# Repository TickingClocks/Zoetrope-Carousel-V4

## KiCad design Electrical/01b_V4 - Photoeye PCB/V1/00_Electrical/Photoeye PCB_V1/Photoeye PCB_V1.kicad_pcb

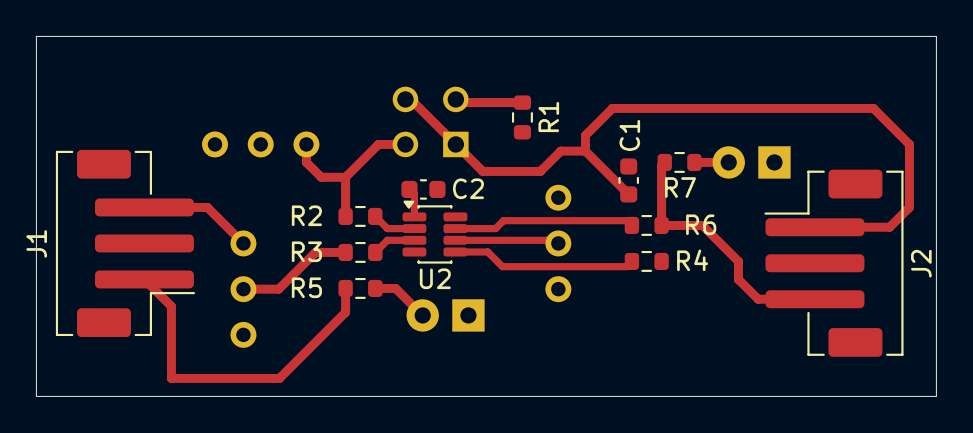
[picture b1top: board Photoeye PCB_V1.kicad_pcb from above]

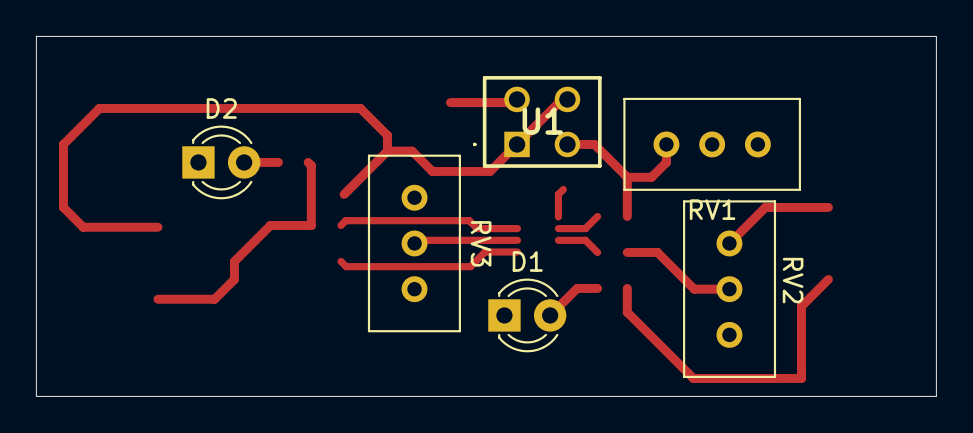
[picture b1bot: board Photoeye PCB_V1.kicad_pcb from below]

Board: 2 copper layers, 50.0 x 20.0 mm, 18 parts (6 on the bottom side), 15 nets.

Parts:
C1: 0.1uF 0603; C_0603_1608Metric
C2: cap; C_0603_1608Metric
D1: YELLOW_3mm_LED; LED_D3.0mm_Clear
D2: GREEN_3mm_TH; LED_D3.0mm
J1, J2: B3B-PH-SM4-TB(LF)(SN); JST_PH_B3B-PH-SM4-TB_1x03-1MP_P2.00mm_Vertical
R1: 100ohm_0603; R_0603_1608Metric
R2, R3, R4, R6: 1kohm_0603; R_0603_1608Metric
R5: ohm_0603; R_0603_1608Metric
R7: 300ohm_0603; R_0603_1608Metric
RV1: 100kohm pot; Potentiometer_Bourns_3296W_Vertical
RV2, RV3: R_Potentiometer_US; Potentiometer_Bourns_3296W_Vertical
U1: RPR-220; RPR220
U2: LM358B; SOT-23-8

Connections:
+3.3V: C1.1, J1.1, J2.1, R5.1, RV3.1, U1.1 (A), U1.3 (E), U2.8 (V+)
/outputState: J2.3, R6.1, R7.2
/platterSensor: R2.2, RV1.1, U1.4 (C)
GND: C1.2, C2.1, D1.1 (K), D2.1 (K), J1.2, J1.MP (Pin_1), J2.2, J2.MP (Pin_1), R1.1, RV1.2, RV2.3, RV3.3, U2.4 (V-)
unnamed: C2.2, R4.2, U2.1
unnamed: D1.2 (A), R5.2
unnamed: D2.2 (A), R7.1
unnamed: J1.3, RV2.1
unnamed: R3.2, RV2.2
unnamed: R6.2, U2.7
unnamed: R1.2, U1.2 (K)
unnamed: R3.1, U2.3 (+)
unnamed: R2.1, U2.2 (-)
unnamed: R4.1, U2.5 (+)
unnamed: RV3.2, U2.6 (-)

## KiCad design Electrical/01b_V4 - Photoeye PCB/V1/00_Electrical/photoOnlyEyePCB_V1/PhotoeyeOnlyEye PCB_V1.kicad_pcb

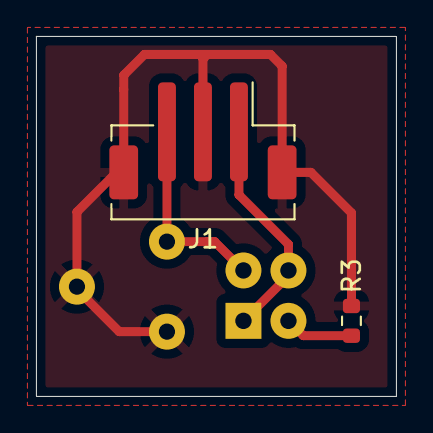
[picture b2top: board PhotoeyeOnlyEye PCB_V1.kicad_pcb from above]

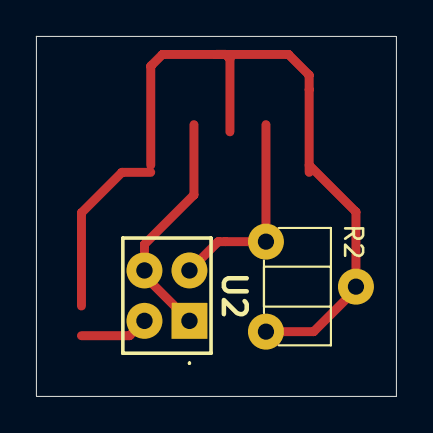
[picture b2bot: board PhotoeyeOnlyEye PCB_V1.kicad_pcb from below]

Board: 2 copper layers, 20.0 x 20.0 mm, 4 parts (2 on the bottom side), 4 nets.

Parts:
J1: B3B-PH-SM4-TB(LF)(SN); JST_PH_B3B-PH-SM4-TB_1x03-1MP_P2.00mm_Vertical
R2: 100k_TH_Pot; Potentiometer_TH
R3: 100ohm_0603; R_0603_1608Metric
U2: RPR-220; RPR220

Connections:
+3.3V: J1.1, U2.1 (A), U2.3 (E)
/sensorValue: J1.3, R2.1, U2.4 (C)
GND: J1.2, J1.MP (Pin_1), R2.2, R2.3, R3.1
unnamed: R3.2, U2.2 (K)

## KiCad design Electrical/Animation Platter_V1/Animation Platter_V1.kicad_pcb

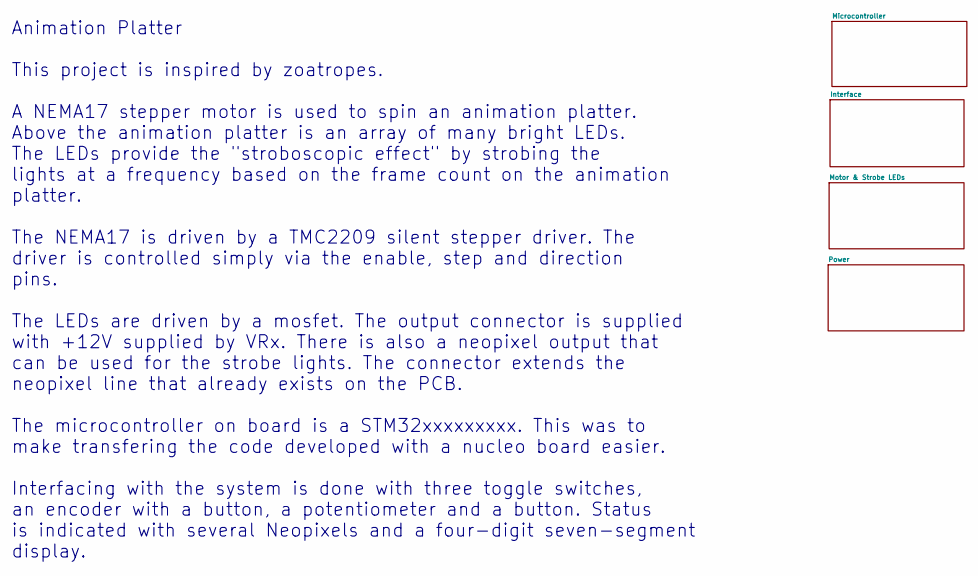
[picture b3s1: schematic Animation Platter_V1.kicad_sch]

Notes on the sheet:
Animation Platter This project is inspired by zoatropes. A NEMA17 stepper motor is used to spin an animation platter. Above the animation platter is an array of many bright LEDs. The LEDs provide the "stroboscopic effect" by strobing the lights at a frequency based on the frame count on the animati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

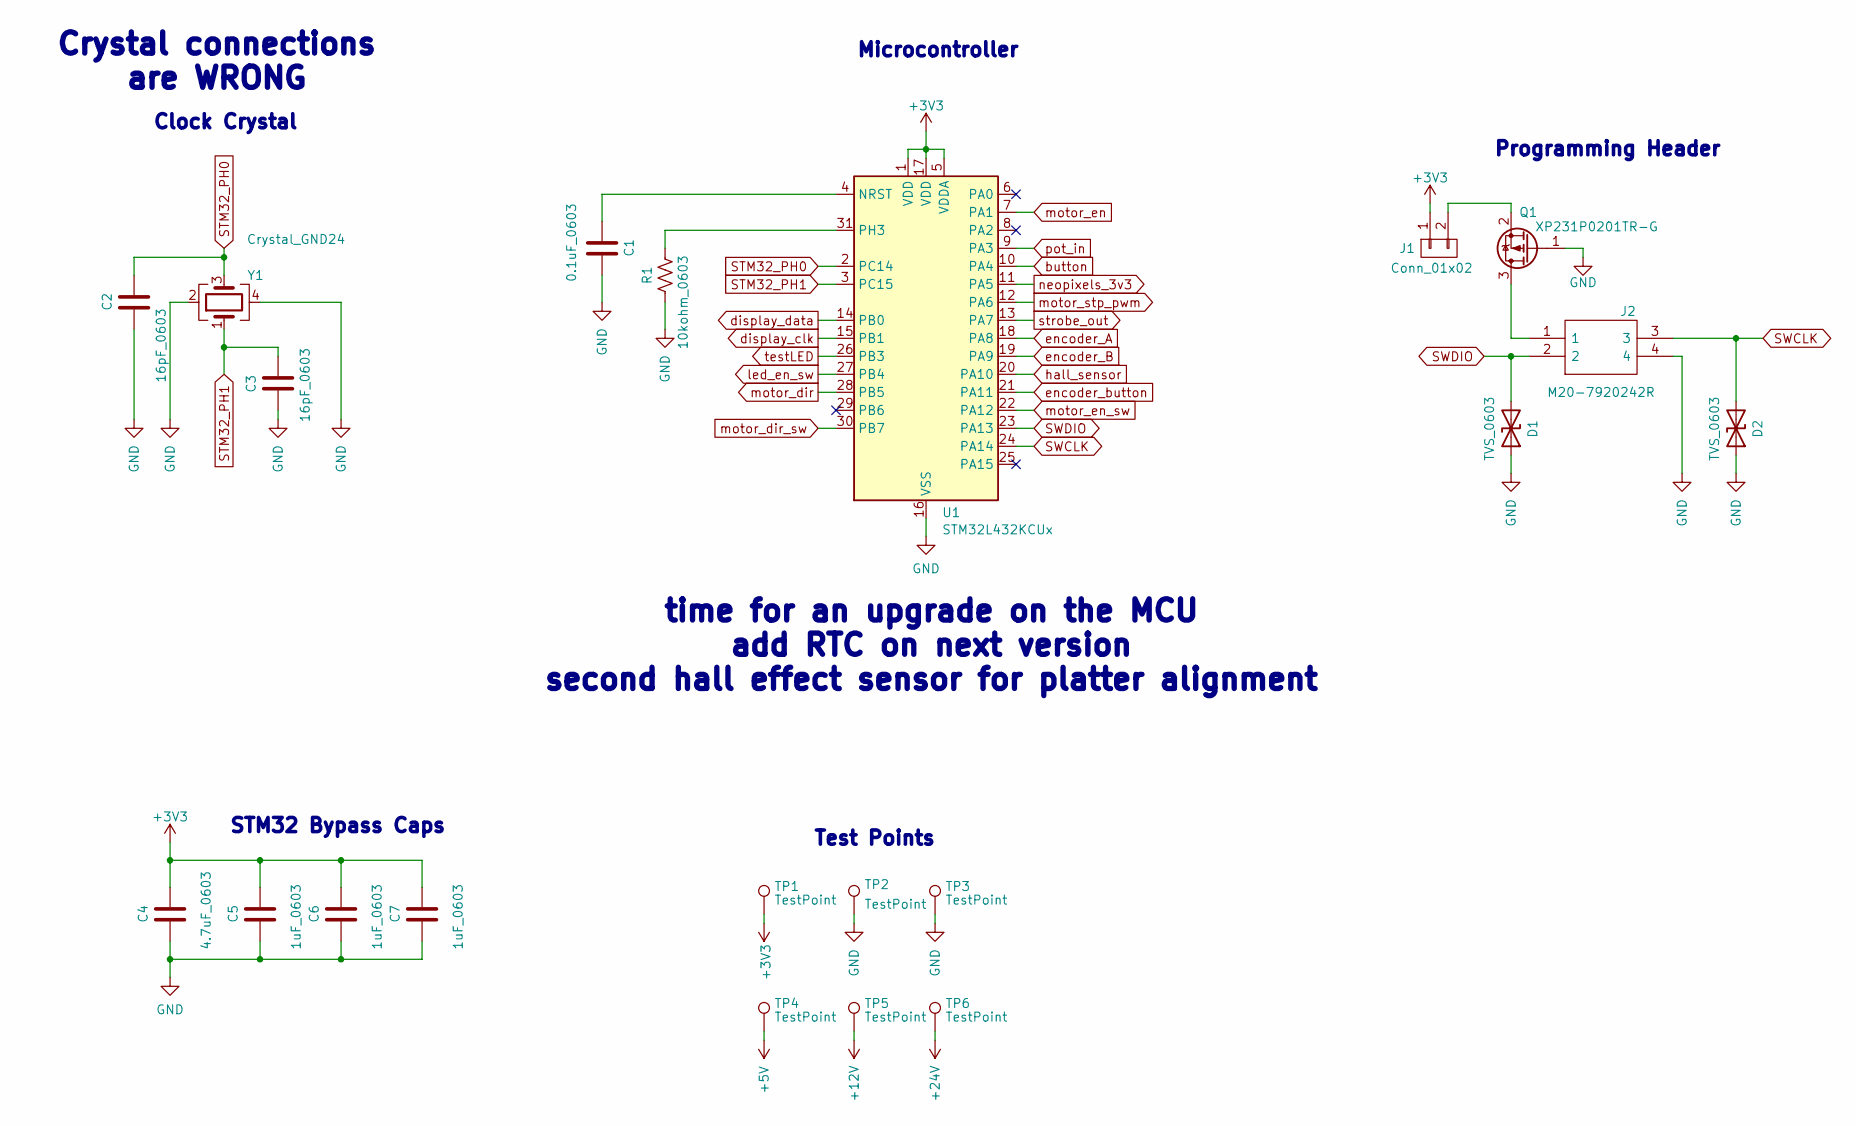
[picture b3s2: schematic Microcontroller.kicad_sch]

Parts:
C1: 0.1uF_0603; C_0603_1608Metric
C2, C3: 16pF_0603; C_0603_1608Metric
C4: 4.7uF_0603; C_0603_1608Metric
C5, C6, C7: 1uF_0603; C_0603_1608Metric
D1, D2: TVS_0603; D_0603_1608Metric
J1: Conn_01x02; PinHeader_1x02_P2.54mm_Vertical
J2: M20-7920242R; M207920242R; Mouser Part Number 855-M20-7920242R
Q1: XP231P0201TR-G; SOT95P240X115-3N
R1: 10kohm_0603; R_0603_1608Metric
TP1, TP4, TP5, TP6: TestPoint; TestPoint_Pad_D1.0mm
TP2, TP3: TestPoint; TestPoint_THTPad_D2.0mm_Drill1.0mm
U1: STM32L432KCUx; QFN-32-1EP_5x5mm_P0.5mm_EP3.45x3.45mm
Y1: Crystal_GND24; Crystal_SMD_2520-4Pin_2.5x2.0mm

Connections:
+3V3: C4.1, C5.1, C6.1, C7.1, J1.1, TP1.1, U1.1 (VDD), U1.5 (VDDA), U1.17 (VDD); also elsewhere on the board
+5V: TP4.1; also elsewhere on the board
+12V: TP5.1; also elsewhere on the board
+24V: TP6.1; also elsewhere on the board
GND: C1.2, C2.2, C3.1, C4.2, C5.2, C6.2, C7.2, D1.1 (A1), D2.1 (A1), J2.4, Q1.1 (G), R1.1, TP2.1, TP3.1, U1.16 (VSS), U1.32 (VSS), U1.33 (VSS), Y1.2, Y1.4; also elsewhere on the board
unnamed: J1.2, Q1.2 (S)
unnamed: J2.1, Q1.3 (D)
unnamed: C1.1, U1.4 (NRST)
unnamed: R1.2, U1.31 (PH3)
STM32_PH0: C2.1, U1.2 (PC14), Y1.3
STM32_PH1: C3.2, U1.3 (PC15), Y1.1
SWCLK: D2.2 (A2), J2.3, U1.24 (PA14)
SWDIO: D1.2 (A2), J2.2, U1.23 (PA13)
button: U1.10 (PA4); also elsewhere on the board
display_clk: U1.15 (PB1); also elsewhere on the board
display_data: U1.14 (PB0); also elsewhere on the board
encoder_A: U1.18 (PA8); also elsewhere on the board
encoder_B: U1.19 (PA9); also elsewhere on the board
encoder_button: U1.21 (PA11); also elsewhere on the board
hall_sensor: U1.20 (PA10); also elsewhere on the board
led_en_sw: U1.27 (PB4); also elsewhere on the board
motor_dir: U1.28 (PB5); also elsewhere on the board
motor_dir_sw: U1.30 (PB7); also elsewhere on the board
motor_en: U1.7 (PA1); also elsewhere on the board
motor_en_sw: U1.22 (PA12); also elsewhere on the board
motor_stp_pwm: U1.12 (PA6); also elsewhere on the board
neopixels_3v3: U1.11 (PA5); also elsewhere on the board
pot_in: U1.9 (PA3); also elsewhere on the board
strobe_out: U1.13 (PA7); also elsewhere on the board
testLED: U1.26 (PB3); also elsewhere on the board

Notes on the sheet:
time for an upgrade on the MCU add RTC on next version second hall effect sensor for platter alignment
STM32 Bypass Caps
Clock Crystal
Crystal connections are WRONG
Microcontroller
Test Points
Programming Header

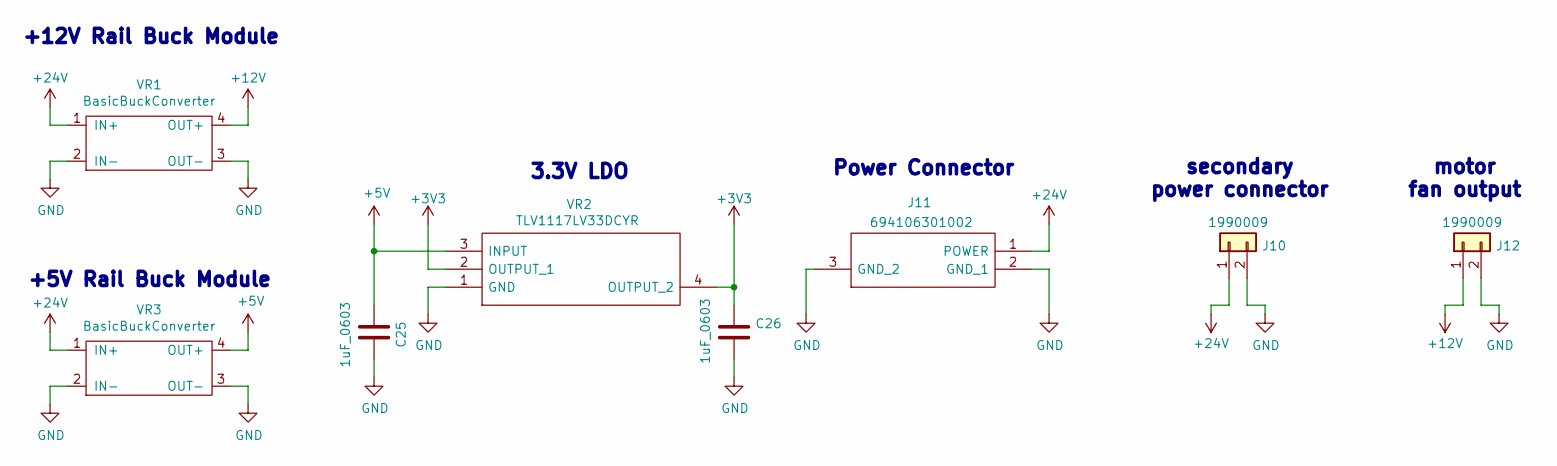
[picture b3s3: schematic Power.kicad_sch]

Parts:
C25, C26: 1uF_0603; C_0603_1608Metric
J10, J12: 1990009
J11: 694106301002; 694106301002_1; Mouser Part Number 710-694106301002
VR1, VR3: BasicBuckConverter; LM2596_Module(43mmx21mm)
VR2: TLV1117LV33DCYR; SOT230P700X180-4N; Mouser Part Number 595-TLV1117LV33DCYR

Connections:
+3V3: C26.2, VR2.2 (OUTPUT_1), VR2.4 (OUTPUT_2); also elsewhere on the board
+5V: C25.2, VR2.3 (INPUT), VR3.4 (OUT+); also elsewhere on the board
+12V: J12.1, VR1.4 (OUT+); also elsewhere on the board
+24V: J10.1, J11.1 (POWER), VR1.1 (IN+), VR3.1 (IN+); also elsewhere on the board
GND: C25.1, C26.1, J10.2, J11.2 (GND_1), J11.3 (GND_2), J12.2, VR1.2 (IN-), VR1.3 (OUT-), VR2.1 (GND), VR3.2 (IN-), VR3.3 (OUT-); also elsewhere on the board

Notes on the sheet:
+12V Rail Buck Module
+5V Rail Buck Module
secondary power connector
3.3V LDO
motor fan output
Power Connector

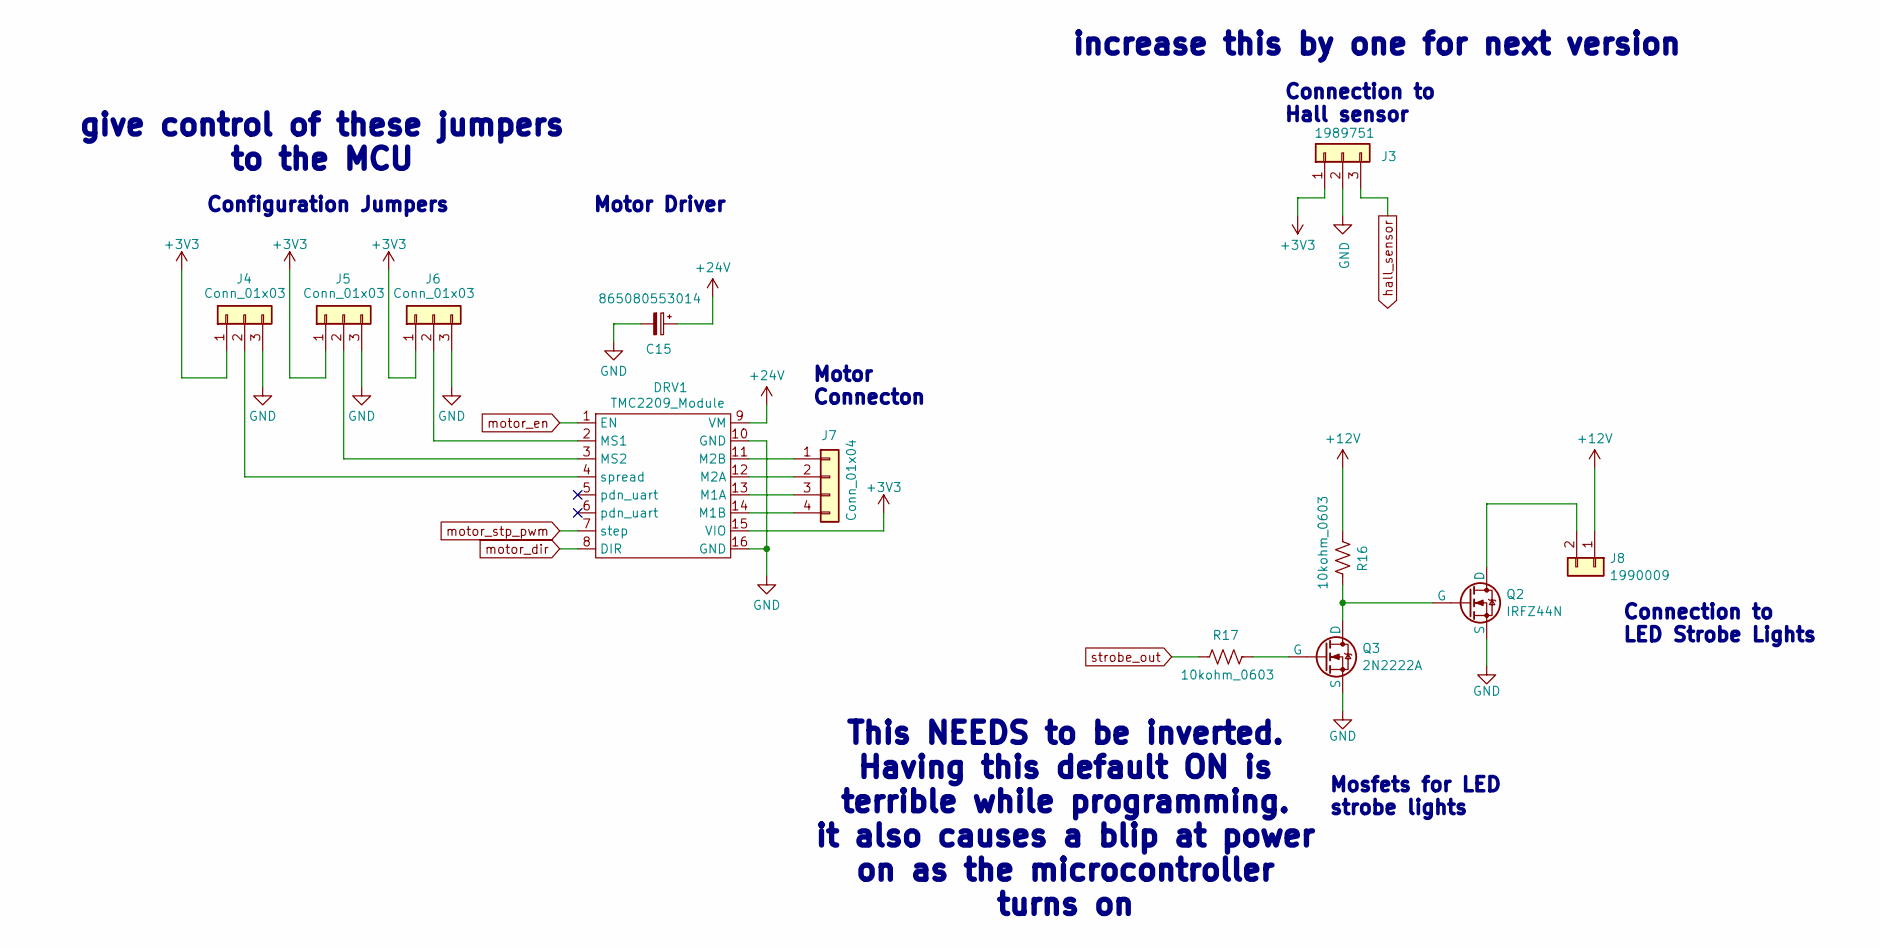
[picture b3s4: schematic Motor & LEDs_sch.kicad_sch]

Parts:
C15: 865080553014; CAPAE830X1050N
DRV1: TMC2209_Module
J3: 1989751
J4, J5, J6: Conn_01x03; PinHeader_1x03_P2.54mm_Vertical
J7: Conn_01x04; PinHeader_1x04_P2.54mm_Vertical
J8: 1990009
Q2: IRFZ44N; IRFZ44NSTRLPBF
Q3: 2N2222A; TO-92
R16, R17: 10kohm_0603; R_0603_1608Metric

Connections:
+3V3: DRV1.15 (VIO), J3.1, J4.1, J5.1, J6.1; also elsewhere on the board
+12V: J8.1, R16.1; also elsewhere on the board
+24V: C15.1, DRV1.9 (VM); also elsewhere on the board
GND: C15.2, DRV1.10 (GND), DRV1.16 (GND), J3.2, J4.3, J5.3, J6.3, Q2.3 (S), Q3.1 (S); also elsewhere on the board
unnamed: DRV1.13 (M1A), J7.3
unnamed: DRV1.14 (M1B), J7.4
unnamed: DRV1.12 (M2A), J7.2
unnamed: DRV1.11 (M2B), J7.1
unnamed: DRV1.2 (MS1), J6.2
unnamed: DRV1.3 (MS2), J5.2
unnamed: DRV1.4 (spread), J4.2
unnamed: J8.2, Q2.2 (D)
unnamed: Q2.1 (G), Q3.3 (D), R16.2
unnamed: Q3.2 (G), R17.2
hall_sensor: J3.3; also elsewhere on the board
motor_dir: DRV1.8 (DIR); also elsewhere on the board
motor_en: DRV1.1 (EN); also elsewhere on the board
motor_stp_pwm: DRV1.7 (step); also elsewhere on the board
strobe_out: R17.1; also elsewhere on the board

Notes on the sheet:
Motor Driver
Connection to LED Strobe Lights
Connection to Hall sensor
Configuration Jumpers
This NEEDS to be inverted. Having this default ON is terrible while programming. it also causes a blip at power on as the microcontroller turns on
Motor Connecton
Mosfets for LED strobe lights
increase this by one for next version
give control of these jumpers to the MCU

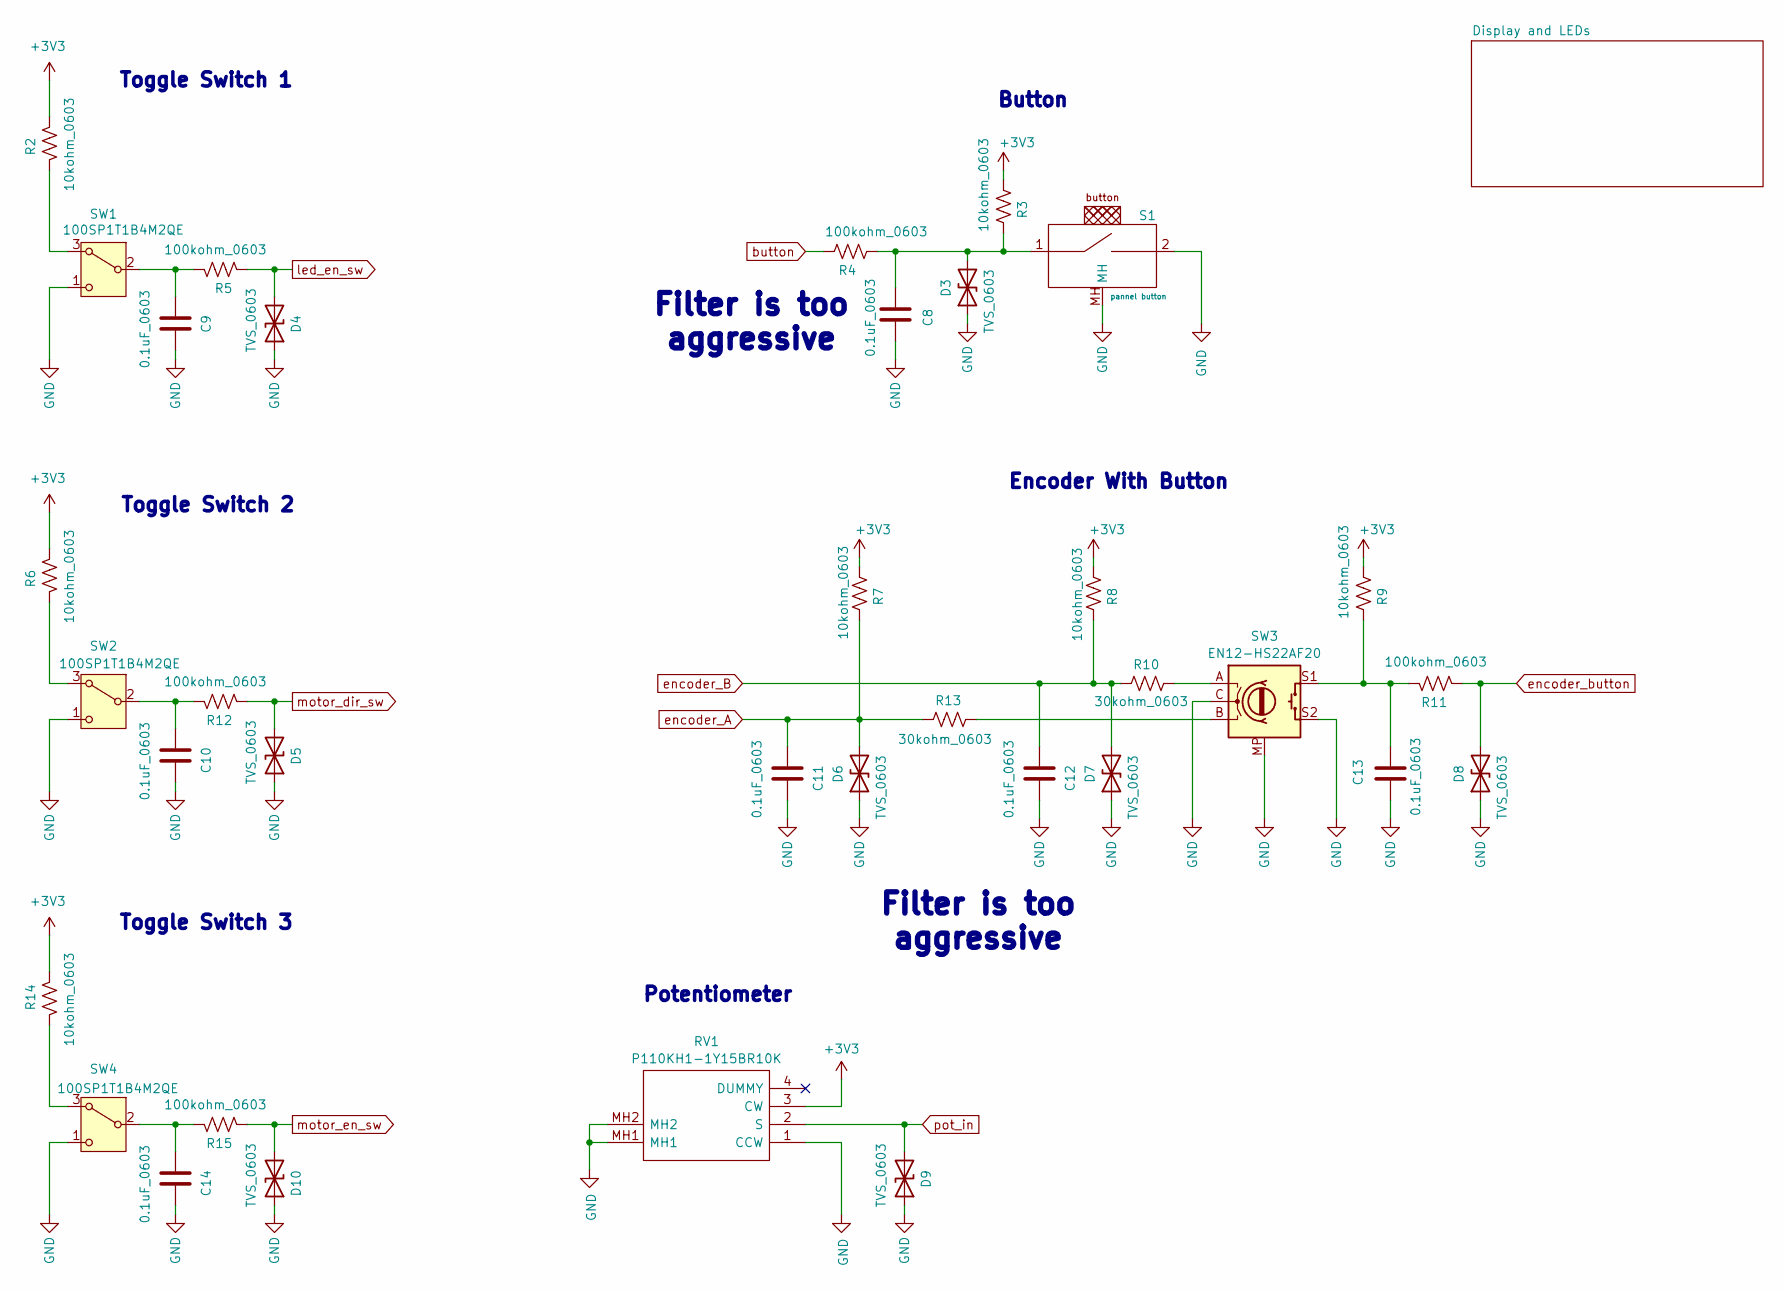
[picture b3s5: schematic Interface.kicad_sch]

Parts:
C8, C9, C10, C11, C12, C13, C14: 0.1uF_0603; C_0603_1608Metric
D3, D4, D5, D6, D7, D8, D9, D10: TVS_0603; D_0603_1608Metric
R2, R3, R6, R7, R8, R9, R14: 10kohm_0603; R_0603_1608Metric
R4, R5, R11, R12, R15: 100kohm_0603; R_0603_1608Metric
R10, R13: 30kohm_0603; R_0603_1608Metric
RV1: P110KH1-1Y15BR10K; P110KH11Y15BR10K; Mouser Part Number 858-P110KH11Y15BR10K
S1: pannel button; 10mm_pannel_button
SW1, SW2, SW4: 100SP1T1B4M2QE
SW3: EN12-HS22AF20; EN12HS22AF20

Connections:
+3V3: R2.1, R3.1, R6.1, R7.1, R8.1, R9.1, R14.1, RV1.3 (CW); also elsewhere on the board
GND: C8.2, C9.1, C10.1, C11.1, C12.1, C13.2, C14.1, D3.1 (A1), D4.1 (A1), D5.1 (A1), D6.1 (A1), D7.1 (A1), D8.1 (A1), D9.1 (A1), D10.1 (A1), RV1.1 (CCW), RV1.MH1, RV1.MH2, S1.2, S1.MH, SW1.1 (C), SW2.1 (C), SW3.C, SW3.MP, SW3.S2, SW4.1 (C); also elsewhere on the board
unnamed: C13.1, R9.2, R11.1, SW3.S1
unnamed: C8.1, D3.2 (A2), R3.2, R4.1, S1.1
unnamed: R10.2, SW3.A
unnamed: R13.2, SW3.B
unnamed: R2.2, SW1.3 (A)
unnamed: C9.2, R5.1, SW1.2 (B)
unnamed: R6.2, SW2.3 (A)
unnamed: C10.2, R12.1, SW2.2 (B)
unnamed: R14.2, SW4.3 (A)
unnamed: C14.2, R15.1, SW4.2 (B)
button: R4.2; also elsewhere on the board
encoder_A: C11.2, D6.2 (A2), R7.2, R13.1; also elsewhere on the board
encoder_B: C12.2, D7.2 (A2), R8.2, R10.1; also elsewhere on the board
encoder_button: D8.2 (A2), R11.2; also elsewhere on the board
led_en_sw: D4.2 (A2), R5.2; also elsewhere on the board
motor_dir_sw: D5.2 (A2), R12.2; also elsewhere on the board
motor_en_sw: D10.2 (A2), R15.2; also elsewhere on the board
pot_in: D9.2 (A2), RV1.2 (S); also elsewhere on the board

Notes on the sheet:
Encoder With Button
Filter is too aggressive
Button
Toggle Switch 1
Potentiometer
Toggle Switch 2
Toggle Switch 3

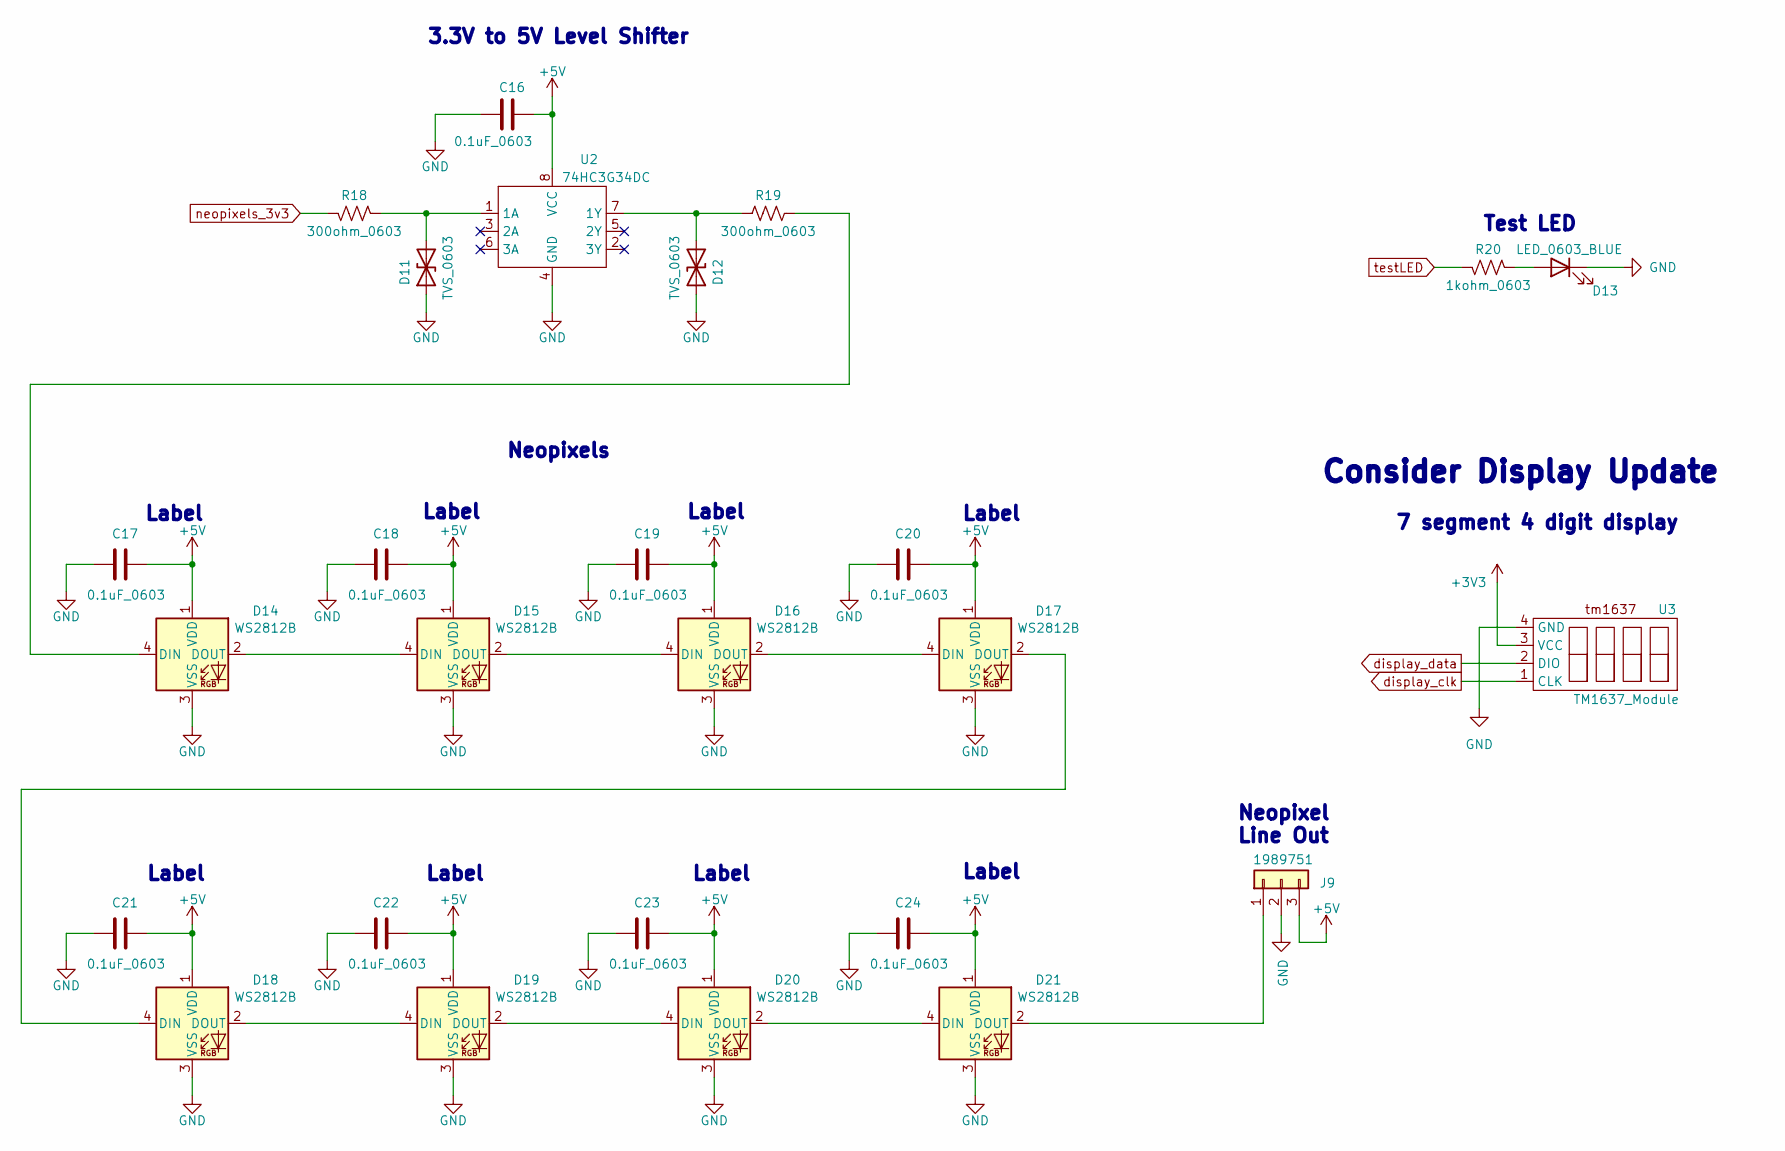
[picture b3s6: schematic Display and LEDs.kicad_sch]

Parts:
C16, C17, C18, C19, C20, C21, C22, C23, C24: 0.1uF_0603; C_0603_1608Metric
D11, D12: TVS_0603; R_0603_1608Metric
D13: LED_0603_BLUE; LED_0603_1608Metric
D14, D15, D16, D17, D18, D19, D20, D21: WS2812B; LED_WS2812B_PLCC4_5.0x5.0mm_P3.2mm
J9: 1989751
R18, R19: 300ohm_0603; R_0603_1608Metric
R20: 1kohm_0603; R_0603_1608Metric
U2: 74HC3G34DC; 75HC3G34DC
U3: TM1637_Module; TM1637_module

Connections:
+3V3: U3.3 (VCC); also elsewhere on the board
+5V: C16.1, C17.1, C18.1, C19.1, C20.1, C21.1, C22.1, C23.1, C24.1, D14.1 (VDD), D15.1 (VDD), D16.1 (VDD), D17.1 (VDD), D18.1 (VDD), D19.1 (VDD), D20.1 (VDD), D21.1 (VDD), J9.3, U2.8 (VCC); also elsewhere on the board
GND: C16.2, C17.2, C18.2, C19.2, C20.2, C21.2, C22.2, C23.2, C24.2, D11.1 (A1), D12.1 (A1), D13.1 (K), D14.3 (VSS), D15.3 (VSS), D16.3 (VSS), D17.3 (VSS), D18.3 (VSS), D19.3 (VSS), D20.3 (VSS), D21.3 (VSS), J9.2, U2.4 (GND), U3.4 (GND); also elsewhere on the board
unnamed: D11.2 (A2), R18.1, U2.1 (1A)
unnamed: D12.2 (A2), R19.2, U2.7 (1Y)
unnamed: D13.2 (A), R20.1
unnamed: D14.4 (DIN), R19.1
unnamed: D14.2 (DOUT), D15.4 (DIN)
unnamed: D15.2 (DOUT), D16.4 (DIN)
unnamed: D16.2 (DOUT), D17.4 (DIN)
unnamed: D17.2 (DOUT), D18.4 (DIN)
unnamed: D18.2 (DOUT), D19.4 (DIN)
unnamed: D19.2 (DOUT), D20.4 (DIN)
unnamed: D20.2 (DOUT), D21.4 (DIN)
unnamed: D21.2 (DOUT), J9.1
display_clk: U3.1 (CLK); also elsewhere on the board
display_data: U3.2 (DIO); also elsewhere on the board
neopixels_3v3: R18.2; also elsewhere on the board
testLED: R20.2; also elsewhere on the board

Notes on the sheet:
Label
Neopixel Line Out
7 segment 4 digit display
Consider Display Update
Neopixels
Test LED
3.3V to 5V Level Shifter

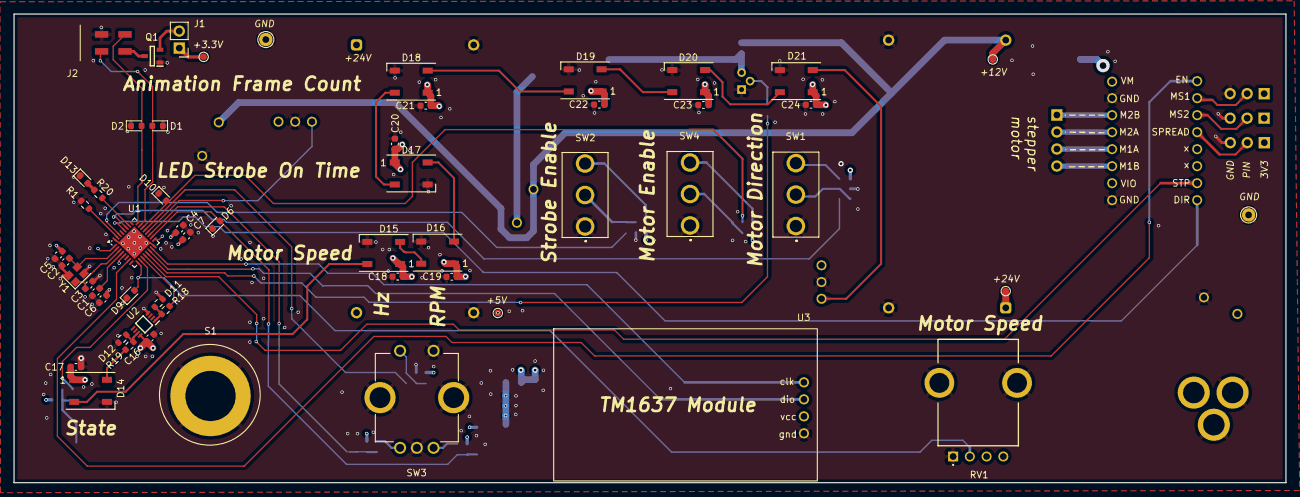
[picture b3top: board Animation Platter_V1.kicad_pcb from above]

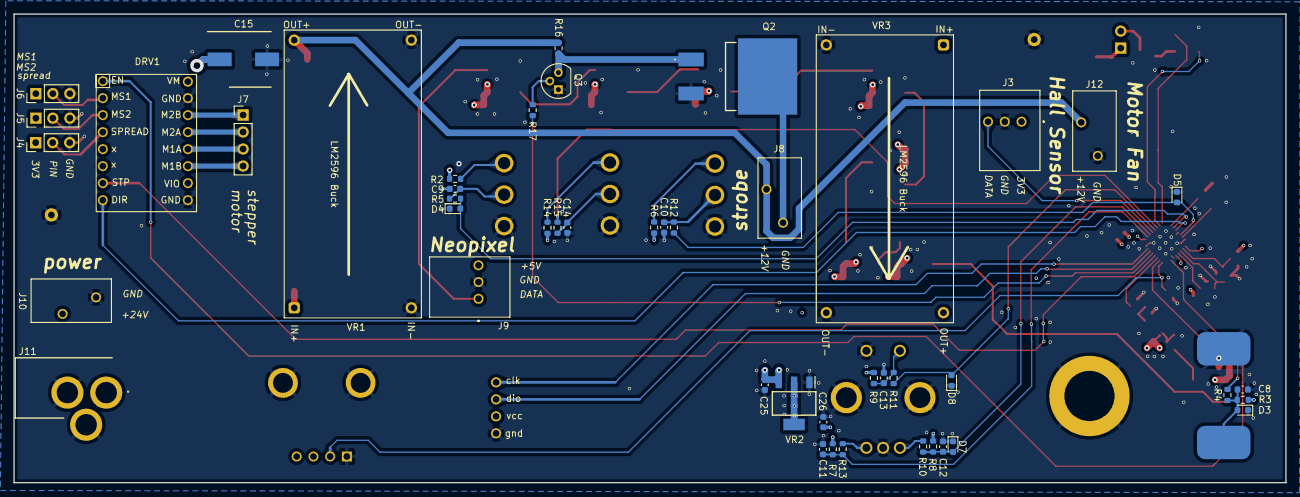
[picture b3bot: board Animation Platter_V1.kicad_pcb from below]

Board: 4 copper layers, 190.0 x 70.0 mm, 102 parts (47 on the bottom side), 62 nets.
